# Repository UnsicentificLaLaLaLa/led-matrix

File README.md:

# led-matrix

[TOC]

## 介绍

基于 MM32G0001 设计的 LED 点阵屏模块，可级联，通过串口控制。

## 使用方法

### 单个模块

连接 VCC（3.3 ~ 5V），GND，DIN 引脚连接串口的 TXD。

串口配置为 1000000 波特率，8bit 数据，1停止位，无奇偶校验位。

串口发送 8 个 0xFF，则可以点亮所有 led，发送 8 个 0x00，则会熄灭所有 led。

帧内发送数据的间隔需要小于 1.5ms，每两帧数据之间的间隔需要大于 2ms。

### 多个模块

下一个模块的 VCC 连接 上一个模块的 VCC，GND 连接 GND，DIN 连接 DOUT。第一个模块的连接同单个模块。

串口配置为 1000000 波特率，8bit 数据，1停止位，无奇偶校验位。

串口发送 8\*n 个 0xFF，则可以点亮所有 led，发送 8\*n 个 0x00，则会熄灭所有 led；n 为模块数量。

帧内发送数据的间隔需要小于 1.5ms，每两帧数据之间的间隔需要大于 2ms。

### 更新固件

上电前，保证模块的 DIN 引脚为低电平，然后上电，可进入等待下载固件的状态。

模块背面的 D 触点为 SWDIO，C 为 SWCLK，G 为 GND，使用 SWD 方式下载固件。

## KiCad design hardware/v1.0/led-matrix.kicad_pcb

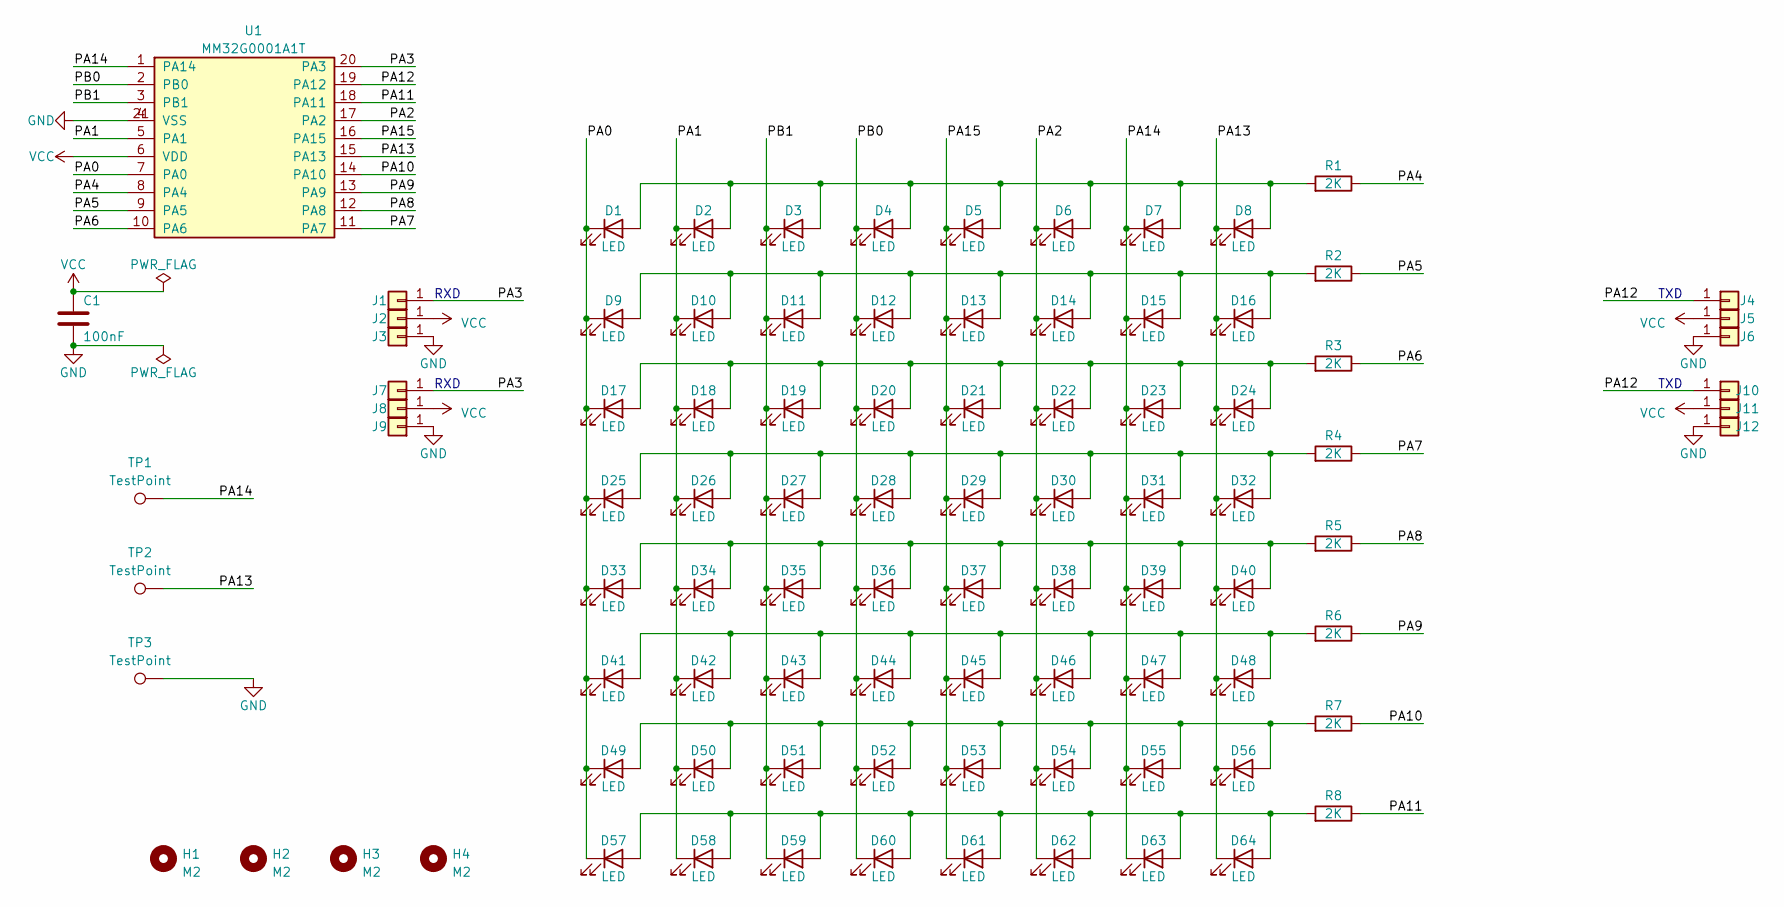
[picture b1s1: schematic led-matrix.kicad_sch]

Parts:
C1: 100nF; C_0603_1608Metric_Pad1.08x0.95mm_HandSolder
D1, D2, D3, D4, D5, D6, D7, D8, D9, D10, D11, D12, D13, D14, D15, D16, D17, D18, D19, D20, D21, D22, D23, D24, D25, D26, D27, D28, D29, D30, D31, D32, D33, D34, D35, D36, D37, D38, D39, D40, D41, D42, D43, D44, D45, D46, D47, D48, D49, D50, D51, D52, D53, D54, D55, D56, D57, D58, D59, D60, D61, D62, D63, D64: LED; LED_0603_1608Metric_Pad1.05x0.95mm_HandSolder
H1, H2, H3, H4: M2; MountingHole_2mm
J1, J2, J3, J4, J5, J6, J7, J8, J9, J10, J11, J12: Conn_01x01; TestPoint_Pad_2.0x2.0mm
R1, R2, R3, R4, R5, R6, R7, R8: 2K; R_0603_1608Metric_Pad0.98x0.95mm_HandSolder
TP1, TP2, TP3: TestPoint; TestPoint_Pad_D1.5mm
U1: MM32G0001A1T; QFN-20-1EP_3x3mm_P0.4mm_EP1.65x1.65mm

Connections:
/PA0: D1.1 (K), D9.1 (K), D17.1 (K), D25.1 (K), D33.1 (K), D41.1 (K), D49.1 (K), D57.1 (K), U1.7 (PA0)
/PA1: D2.1 (K), D10.1 (K), D18.1 (K), D26.1 (K), D34.1 (K), D42.1 (K), D50.1 (K), D58.1 (K), U1.5 (PA1)
/PA2: D6.1 (K), D14.1 (K), D22.1 (K), D30.1 (K), D38.1 (K), D46.1 (K), D54.1 (K), D62.1 (K), U1.17 (PA2)
/PA3: J1.1, J7.1, U1.20 (PA3)
/PA4: R1.1, U1.8 (PA4)
/PA5: R2.1, U1.9 (PA5)
/PA6: R3.1, U1.10 (PA6)
/PA7: R4.1, U1.11 (PA7)
/PA8: R5.1, U1.12 (PA8)
/PA9: R6.1, U1.13 (PA9)
/PA10: R7.1, U1.14 (PA10)
/PA11: R8.1, U1.18 (PA11)
/PA12: J4.1, J10.1, U1.19 (PA12)
/PA13: D8.1 (K), D16.1 (K), D24.1 (K), D32.1 (K), D40.1 (K), D48.1 (K), D56.1 (K), D64.1 (K), TP2.1, U1.15 (PA13)
/PA14: D7.1 (K), D15.1 (K), D23.1 (K), D31.1 (K), D39.1 (K), D47.1 (K), D55.1 (K), D63.1 (K), TP1.1, U1.1 (PA14)
/PA15: D5.1 (K), D13.1 (K), D21.1 (K), D29.1 (K), D37.1 (K), D45.1 (K), D53.1 (K), D61.1 (K), U1.16 (PA15)
/PB0: D4.1 (K), D12.1 (K), D20.1 (K), D28.1 (K), D36.1 (K), D44.1 (K), D52.1 (K), D60.1 (K), U1.2 (PB0)
/PB1: D3.1 (K), D11.1 (K), D19.1 (K), D27.1 (K), D35.1 (K), D43.1 (K), D51.1 (K), D59.1 (K), U1.3 (PB1)
GND: C1.2, J3.1, J6.1, J9.1, J12.1, TP3.1, U1.4 (VSS), U1.21 (VSS)
unnamed: D1.2 (A), D2.2 (A), D3.2 (A), D4.2 (A), D5.2 (A), D6.2 (A), D7.2 (A), D8.2 (A), R1.2
unnamed: D9.2 (A), D10.2 (A), D11.2 (A), D12.2 (A), D13.2 (A), D14.2 (A), D15.2 (A), D16.2 (A), R2.2
unnamed: D17.2 (A), D18.2 (A), D19.2 (A), D20.2 (A), D21.2 (A), D22.2 (A), D23.2 (A), D24.2 (A), R3.2
unnamed: D25.2 (A), D26.2 (A), D27.2 (A), D28.2 (A), D29.2 (A), D30.2 (A), D31.2 (A), D32.2 (A), R4.2
unnamed: D33.2 (A), D34.2 (A), D35.2 (A), D36.2 (A), D37.2 (A), D38.2 (A), D39.2 (A), D40.2 (A), R5.2
unnamed: D41.2 (A), D42.2 (A), D43.2 (A), D44.2 (A), D45.2 (A), D46.2 (A), D47.2 (A), D48.2 (A), R6.2
unnamed: D49.2 (A), D50.2 (A), D51.2 (A), D52.2 (A), D53.2 (A), D54.2 (A), D55.2 (A), D56.2 (A), R7.2
unnamed: D57.2 (A), D58.2 (A), D59.2 (A), D60.2 (A), D61.2 (A), D62.2 (A), D63.2 (A), D64.2 (A), R8.2
VCC: C1.1, J2.1, J5.1, J8.1, J11.1, U1.6 (VDD)

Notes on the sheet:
RXD
TXD

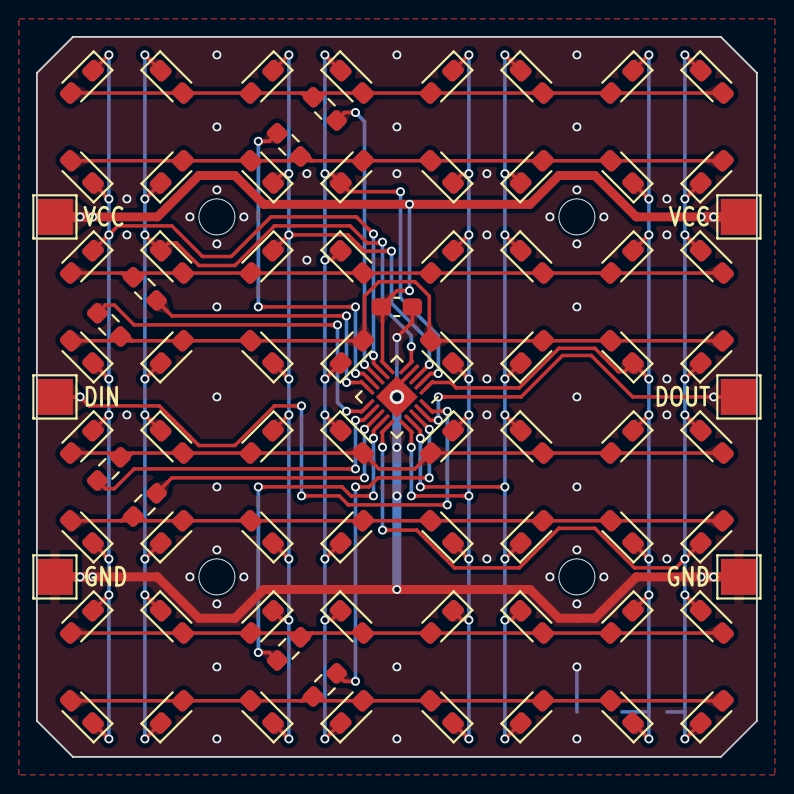
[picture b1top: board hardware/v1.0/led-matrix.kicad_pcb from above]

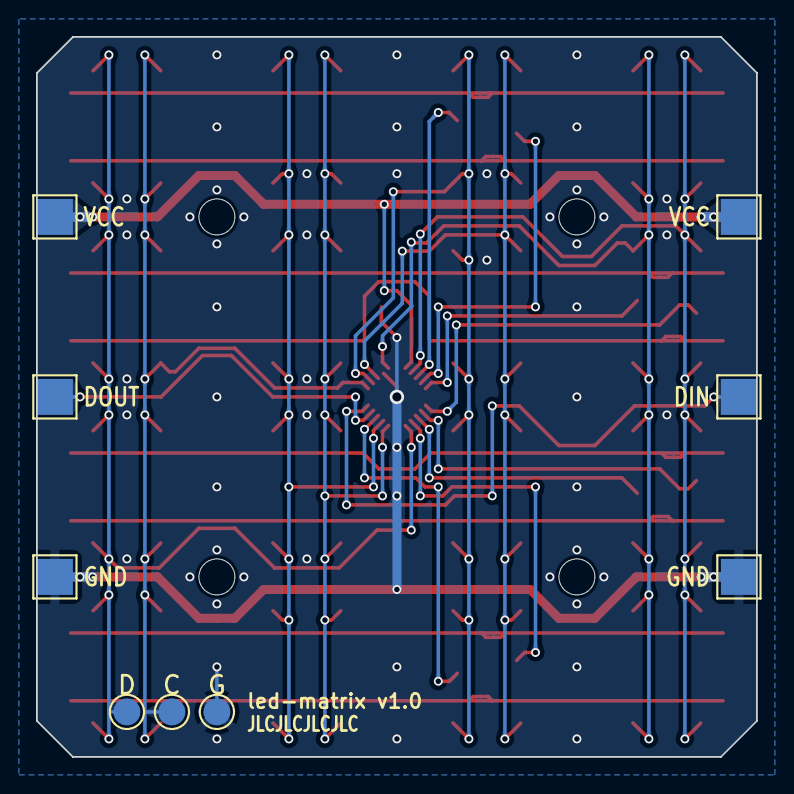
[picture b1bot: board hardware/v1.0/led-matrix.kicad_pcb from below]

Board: 2 copper layers, 40.0 x 40.0 mm, 93 parts (9 on the bottom side), 28 nets.

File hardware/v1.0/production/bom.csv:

Designator,Footprint,Quantity,Value,LCSC Part #
C1,0603,1,100nF,
"D1, D10, D11, D12, D13, D14, D15, D16, D17, D18, D19, D2, D20, D21, D22, D23, D24, D25, D26, D27, D28, D29, D3, D30, D31, D32, D33, D34, D35, D36, D37, D38, D39, D4, D40, D41, D42, D43, D44, D45, D46, D47, D48, D49, D5, D50, D51, D52, D53, D54, D55, D56, D57, D58, D59, D6, D60, D61, D62, D63, D64, D7, D8, D9",0603,64,LED,
"H1, H2, H3, H4",MountingHole_2mm,4,M2,
"J1, J10, J11, J12, J2, J3, J4, J5, J6, J7, J8, J9",TestPoint_Pad_2.0x2.0mm,12,Conn_01x01,
"R1, R2, R3, R4, R5, R6, R7, R8",0603,8,2K,
"TP1, TP2, TP3",TestPoint_Pad_D1.5mm,3,TestPoint,
U1,QFN-20-1EP_3x3mm_P0.4mm_EP1.65x1.65mm,1,MM32G0001A1N,

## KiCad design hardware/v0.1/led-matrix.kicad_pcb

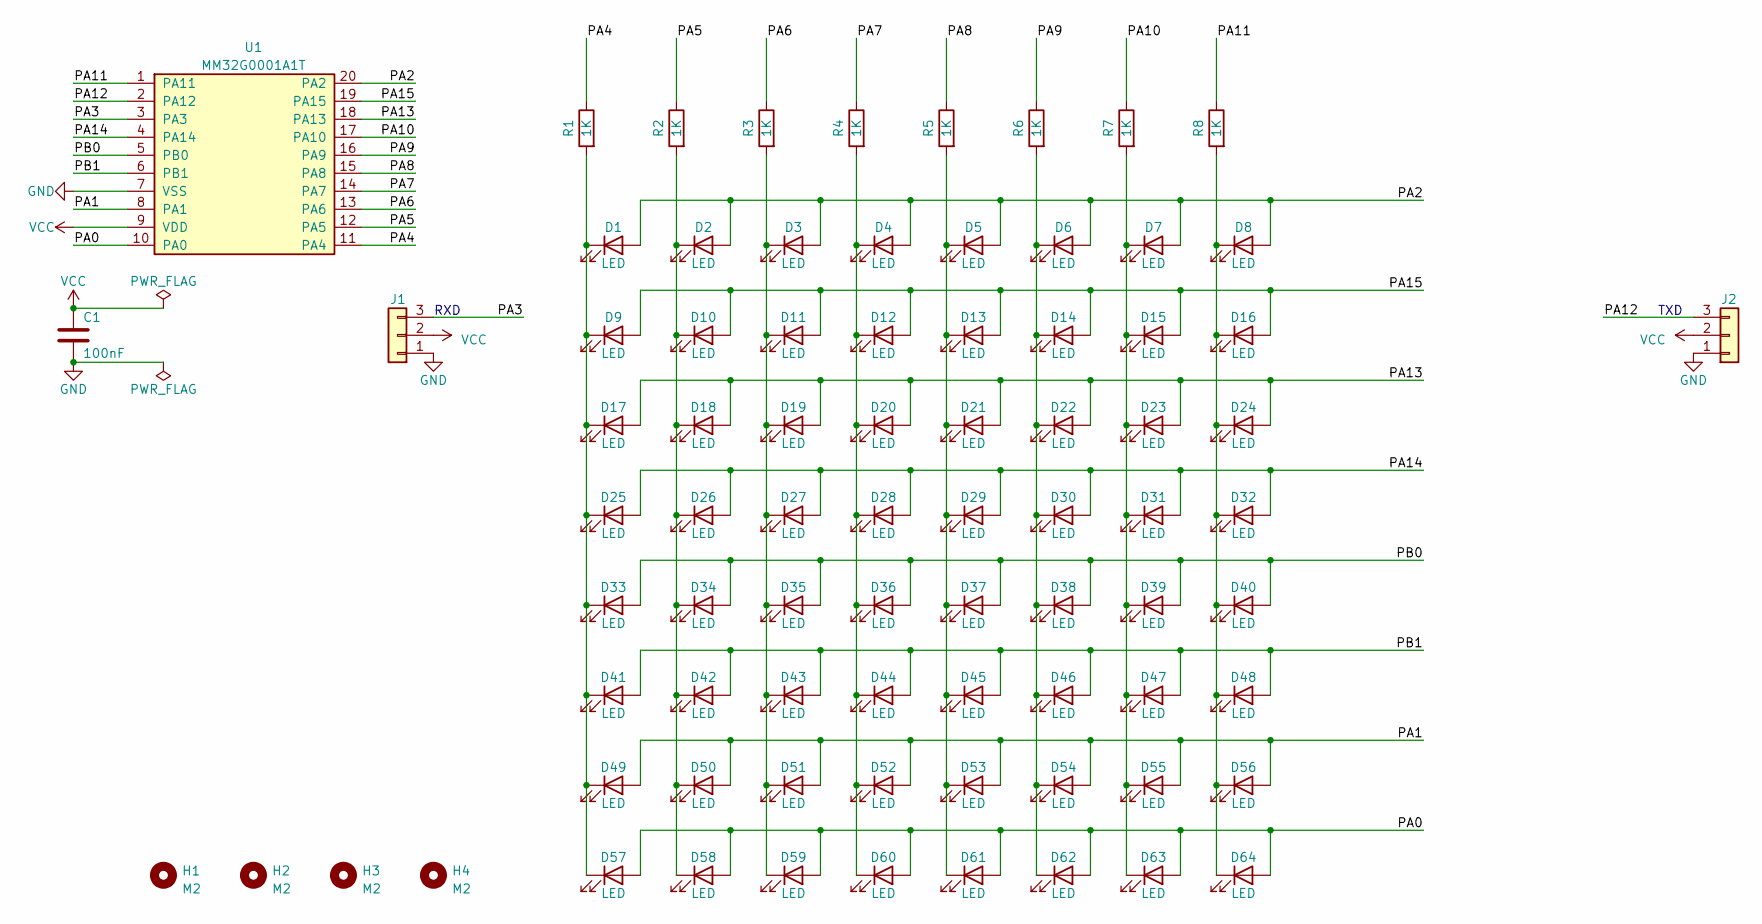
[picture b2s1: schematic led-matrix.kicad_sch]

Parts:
C1: 100nF; C_0603_1608Metric_Pad1.08x0.95mm_HandSolder
D1, D2, D3, D4, D5, D6, D7, D8, D9, D10, D11, D12, D13, D14, D15, D16, D17, D18, D19, D20, D21, D22, D23, D24, D25, D26, D27, D28, D29, D30, D31, D32, D33, D34, D35, D36, D37, D38, D39, D40, D41, D42, D43, D44, D45, D46, D47, D48, D49, D50, D51, D52, D53, D54, D55, D56, D57, D58, D59, D60, D61, D62, D63, D64: LED; LED_0603_1608Metric_Pad1.05x0.95mm_HandSolder
H1, H2, H3, H4: M2; MountingHole_2mm
J1, J2: Conn_01x03; PinHeader_1x03_P2.54mm_Vertical
R1, R2, R3, R4, R5, R6, R7, R8: 1K; R_0603_1608Metric_Pad0.98x0.95mm_HandSolder
U1: MM32G0001A1T; TSSOP-20_4.4x6.5mm_P0.65mm

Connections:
/PA0: D57.2 (A), D58.2 (A), D59.2 (A), D60.2 (A), D61.2 (A), D62.2 (A), D63.2 (A), D64.2 (A), U1.10 (PA0)
/PA1: D49.2 (A), D50.2 (A), D51.2 (A), D52.2 (A), D53.2 (A), D54.2 (A), D55.2 (A), D56.2 (A), U1.8 (PA1)
/PA2: D1.2 (A), D2.2 (A), D3.2 (A), D4.2 (A), D5.2 (A), D6.2 (A), D7.2 (A), D8.2 (A), U1.20 (PA2)
/PA3: J1.3, U1.3 (PA3)
/PA4: R1.1, U1.11 (PA4)
/PA5: R2.1, U1.12 (PA5)
/PA6: R3.1, U1.13 (PA6)
/PA7: R4.1, U1.14 (PA7)
/PA8: R5.1, U1.15 (PA8)
/PA9: R6.1, U1.16 (PA9)
/PA10: R7.1, U1.17 (PA10)
/PA11: R8.1, U1.1 (PA11)
/PA12: J2.3, U1.2 (PA12)
/PA13: D17.2 (A), D18.2 (A), D19.2 (A), D20.2 (A), D21.2 (A), D22.2 (A), D23.2 (A), D24.2 (A), U1.18 (PA13)
/PA14: D25.2 (A), D26.2 (A), D27.2 (A), D28.2 (A), D29.2 (A), D30.2 (A), D31.2 (A), D32.2 (A), U1.4 (PA14)
/PA15: D9.2 (A), D10.2 (A), D11.2 (A), D12.2 (A), D13.2 (A), D14.2 (A), D15.2 (A), D16.2 (A), U1.19 (PA15)
/PB0: D33.2 (A), D34.2 (A), D35.2 (A), D36.2 (A), D37.2 (A), D38.2 (A), D39.2 (A), D40.2 (A), U1.5 (PB0)
/PB1: D41.2 (A), D42.2 (A), D43.2 (A), D44.2 (A), D45.2 (A), D46.2 (A), D47.2 (A), D48.2 (A), U1.6 (PB1)
GND: C1.2, J1.1, J2.1, U1.7 (VSS)
unnamed: D1.1 (K), D9.1 (K), D17.1 (K), D25.1 (K), D33.1 (K), D41.1 (K), D49.1 (K), D57.1 (K), R1.2
unnamed: D2.1 (K), D10.1 (K), D18.1 (K), D26.1 (K), D34.1 (K), D42.1 (K), D50.1 (K), D58.1 (K), R2.2
unnamed: D3.1 (K), D11.1 (K), D19.1 (K), D27.1 (K), D35.1 (K), D43.1 (K), D51.1 (K), D59.1 (K), R3.2
unnamed: D4.1 (K), D12.1 (K), D20.1 (K), D28.1 (K), D36.1 (K), D44.1 (K), D52.1 (K), D60.1 (K), R4.2
unnamed: D5.1 (K), D13.1 (K), D21.1 (K), D29.1 (K), D37.1 (K), D45.1 (K), D53.1 (K), D61.1 (K), R5.2
unnamed: D6.1 (K), D14.1 (K), D22.1 (K), D30.1 (K), D38.1 (K), D46.1 (K), D54.1 (K), D62.1 (K), R6.2
unnamed: D7.1 (K), D15.1 (K), D23.1 (K), D31.1 (K), D39.1 (K), D47.1 (K), D55.1 (K), D63.1 (K), R7.2
unnamed: D8.1 (K), D16.1 (K), D24.1 (K), D32.1 (K), D40.1 (K), D48.1 (K), D56.1 (K), D64.1 (K), R8.2
VCC: C1.1, J1.2, J2.2, U1.9 (VDD)

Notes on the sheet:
RXD
TXD

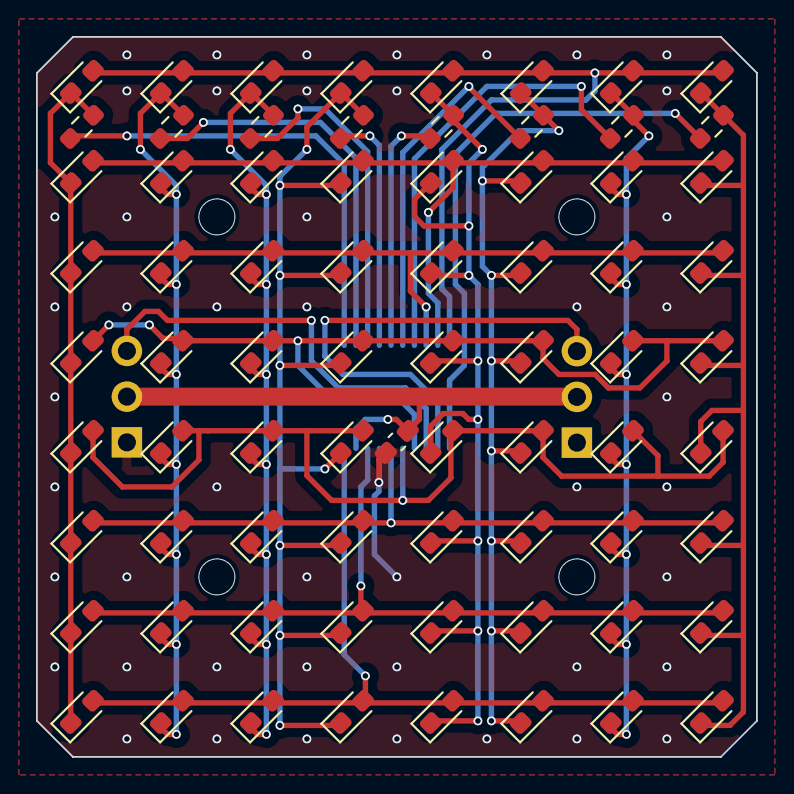
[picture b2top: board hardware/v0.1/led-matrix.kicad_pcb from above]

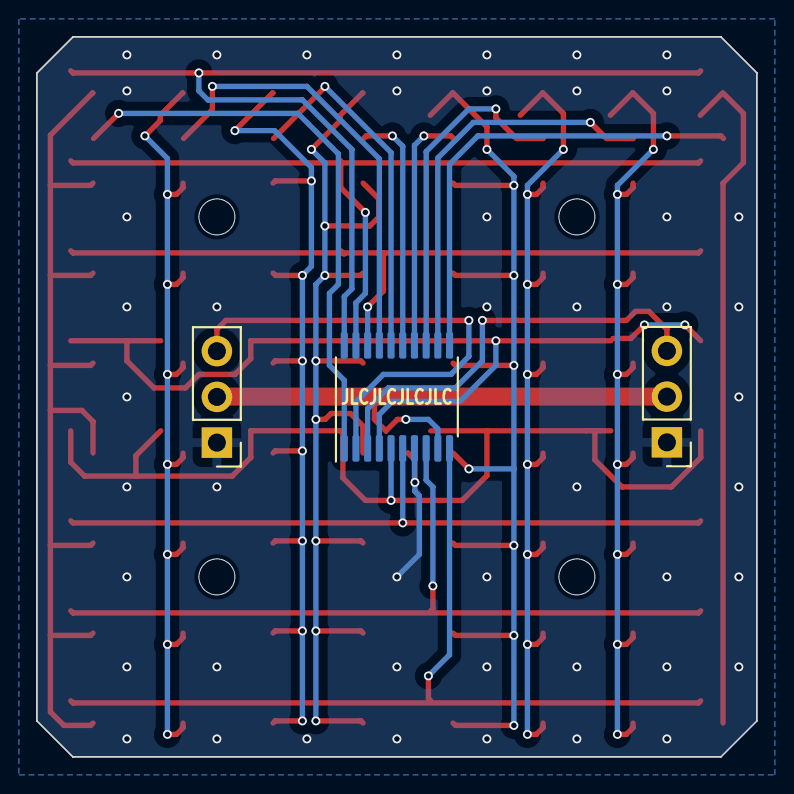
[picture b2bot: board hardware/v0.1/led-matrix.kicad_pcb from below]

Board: 2 copper layers, 40.0 x 40.0 mm, 80 parts (3 on the bottom side), 28 nets.

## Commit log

2023-08-27 update hardware
    - add hardware prj,but not design done.
2023-08-30 hardware done.
    - update pcb.
2023-08-31 add production.
    - add prd.
    - update pcb file.
2023-09-05 add firmware.
    - add led-matrix firmware.
2023-09-05 update readme.
    modify readme.md file
